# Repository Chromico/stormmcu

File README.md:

# Stormmcu Rev 1.4

My website: https://tecknologg.website

Blog post: 

# Front 

# Back

# Assembled board

# Features

# Documentation
You can get the official documentation for stormmcu here: 

# Certification

# Contact

Need to contact me ? Just send me an email at nathan@tecknologg.website or tecknologg@gmail.com

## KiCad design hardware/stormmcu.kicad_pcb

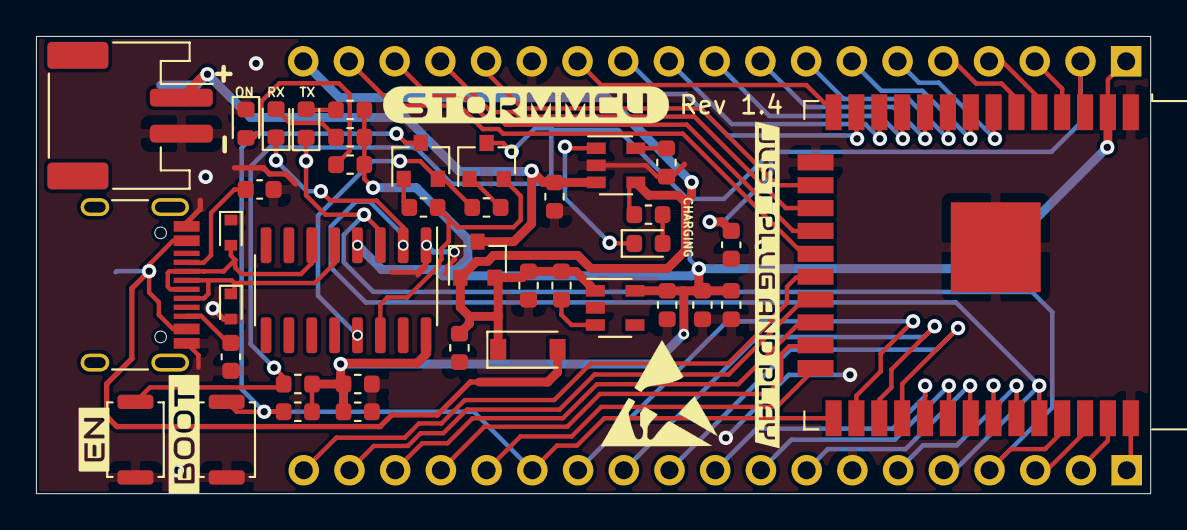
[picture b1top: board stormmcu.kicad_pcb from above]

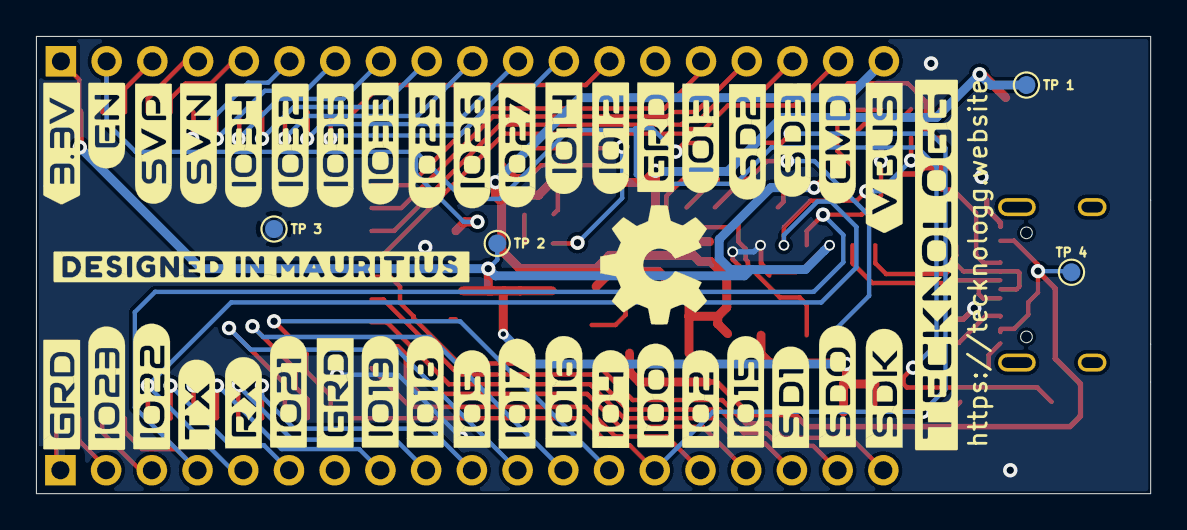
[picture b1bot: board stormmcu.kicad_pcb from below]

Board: 2 copper layers, 61.9 x 25.4 mm, 45 parts (4 on the bottom side), 53 nets.

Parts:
C1, C4, C5, C7: 10uF; C_0603_1608Metric
C2, C3, C6: 100nF; C_0603_1608Metric
C8: 1uF; C_0603_1608Metric
D1, D2: ESD9B5.0ST5G; D_SOD-523
D3: S4; D_SOD-123
D4, D5, D6, D7: LED; LED_0603_1608Metric
J1: USB_C_Receptacle_USB2.0; USB_C_Receptacle_HRO_TYPE-C-31-M-12
J2: Left; PinHeader_1x19_P2.54mm_Vertical
J3: Right; PinHeader_1x19_P2.54mm_Vertical
J4: Conn_01x02_MountingPin; JST_PH_S2B-PH-SM4-TB_1x02-1MP_P2.00mm_Horizontal
Q1: BS250; SOT-23
Q2, Q3: S8050; SOT-23
R1, R9, R10, R11: 1K; R_0603_1608Metric
R2: 2K; R_0603_1608Metric
R3, R4, R5, R6: 10K; R_0603_1608Metric
R7, R8: 100K; R_0603_1608Metric
R12, R13: 5.1K; C_0603_1608Metric
SW1, SW2: SW_Push; SW_Push_SPST_NO_Alps_SKRK
TP 1, TP 2, TP 3, TP 4: TestPoint_Pad_D1.0mm
U1: ESP32-WROOM-32
U2: CH340C; SOP-16_3.9x9.9mm_P1.27mm
U3: LTC4054ES5-4.2; SOT-23-5
U4: AP2112K-3.3; SOT-23-5

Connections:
+3V3: C1.2, C2.2, C3.1, C5.1, C6.1, J2.1, R3.2, R4.1, R9.1, R10.1, R11.1, TP 2.1, U1.2, U2.4, U2.16, U4.5
/CMD: J2.18, U1.19
/DTR: Q2.2, R6.2, U2.13
/EN: C8.1, J2.2, Q3.3, R4.2, SW1.1, U1.3
/IO0: J3.14, Q2.3, R3.1, SW2.1, U1.25
/IO2: J3.15, U1.24
/IO4: J3.13, U1.26
/IO5: J3.10, U1.29
/IO12: J2.13, U1.14
/IO13: J2.15, U1.16
/IO14: J2.12, U1.13
/IO15: J3.16, U1.23
/IO16: J3.12, U1.27
/IO17: J3.11, U1.28
/IO18: J3.9, U1.30
/IO19: J3.8, U1.31
/IO21: J3.6, U1.33
/IO22: J3.3, U1.36
/IO23: J3.2, U1.37
/IO25: J2.9, U1.10
/IO26: J2.10, U1.11
/IO27: J2.11, U1.12
/IO32: J2.7, U1.8
/IO33: J2.8, U1.9
/IO34: J2.5, U1.6
/IO35: J2.6, U1.7
/RTS: Q3.2, R5.2, U2.14
/RXD0: D5.1, J3.5, U1.34, U2.2
/SCK: J3.19, U1.20
/SD0: J3.18, U1.21
/SD1: J3.17, U1.22
/SD2: J2.16, U1.17
/SD3: J2.17, U1.18
/SVN: J2.4, U1.5
/SVP: J2.3, U1.4
/TXD0: D6.1, J3.4, U1.35, U2.3
/VBAT: C7.2, J4.1, Q1.3, TP 1.1, U3.3
/VBUS: D3.2, J1.A4, J1.A9, J1.B4, J1.B9, TP 4.1
/VIN: C4.1, D3.1, J2.19, Q1.1, Q1.2, R1.1, R7.1, R8.1, U3.4, U4.1
GND: C1.1, C2.1, C3.2, C4.2, C5.2, C6.2, C7.1, C8.2, D1.1, D2.2, D7.1, J1.A1, J1.A12, J1.B1, J1.B12, J2.14, J3.1, J3.7, J4.2, R2.2, R7.2, R12.1, R13.1, SW1.2, SW2.2, TP 3.1, U1.1, U1.15, U1.38, U1.39, U2.1, U3.2, U4.2
unnamed: D1.2, J1.A7, J1.B7, U2.6
unnamed: D2.1, J1.A6, J1.B6, U2.5
unnamed: D4.1, U3.1
unnamed: D4.2, R1.2
unnamed: D5.2, R11.2
unnamed: D6.2, R10.2
unnamed: D7.2, R9.2
unnamed: J1.A5, R12.2
unnamed: J1.B5, R13.2
unnamed: Q2.1, R5.1
unnamed: Q3.1, R6.1
unnamed: R2.1, U3.5
unnamed: R8.2, U4.3

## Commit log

2021-10-20 Revision 1.4
2021-10-20 Revert "Revision 1.4 Hardware Design"
2021-10-26 update 1
